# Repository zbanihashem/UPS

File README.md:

# Smart UPS V1

A Raspberry Pi Pico based smart UPS designed for reliable backup power, battery protection, fault monitoring, and system status indication.

The project includes custom PCBs, embedded firmware, sensor monitoring, automatic mains/battery switching, and protection logic.

## V1 Goals

The primary goal of V1 is to build and operate a stable UPS prototype under real load for an extended test period.

V1 is intentionally focused on reliability rather than adding new features. The system is planned to operate for approximately four months so that hardware and firmware issues can be identified before designing V2.

## System Architecture

The system is divided into several functional sections:

- Control Board — Raspberry Pi Pico, RTC, OLED, buzzer and interfaces
- Power Board — power-path control, load switching and power monitoring
- Battery Board — battery temperature and gas monitoring
- LED Board — six system status indicators
- Firmware — fault detection, system policy, power control and display logic

## Firmware Architecture

The firmware is divided into independent modules:

- `Hardware` — low-level GPIO and hardware access
- `Sensors` — sensor acquisition
- `FaultEngine` — fault detection and fault levels
- `SystemPolicy` — system decisions based on detected faults
- `PowerControl` — load, charger and system-power control
- `DisplayManager` — OLED and LED status indication

Main firmware entry point:

`Firmware/UPSPhase1.ino`

## Current V1 Status

The core UPS power-control system is operational.

Verified functions include:

- Automatic startup when mains power is available
- Automatic transition from mains to battery
- Automatic transition back to mains
- Pico self-power hold while operating from battery
- Load disconnect on critical battery condition
- Charger inhibit control
- Complete control-system shutdown on critical battery condition
- Automatic restart when mains power returns
- Mains presence detection
- Battery voltage and current monitoring
- Battery temperature monitoring
- MQ-2 gas monitoring
- OLED status display
- RTC operation
- Buzzer control
- Six front-panel status LEDs

## Status LEDs

The front panel provides six indicators:

- Green — Mains
- Red — Fault
- White — Load
- Blue — Charge Enabled
- Yellow — Battery Operation
- Red — Critical / Danger

The Charge LED represents charger permission from the controller. It does not indicate measured charging current.

## Known V1 Limitations

V1 contains several hardware compromises discovered during integration testing.

These include:

- Passive diode OR power-path architecture
- Relay-based high-side load switching
- Charger module parasitic battery consumption
- Hardware modifications made during integration testing

These issues are being documented for correction in V2.

The current charger isolation issue will be addressed in V1 before extended operation.

## Repository Structure

- `Firmware/` — Raspberry Pi Pico firmware
- `Hardware/` — KiCad schematics, PCB designs and hardware documentation
- `Simulations/` — circuit simulations
- `README.md` — project overview and current status

## Development Strategy

V1 will be operated under real load for approximately four months.

During this period:

- faults and unexpected behavior will be recorded
- hardware modifications will be documented
- firmware changes will be version controlled
- design improvements will be collected for V2

V2 will incorporate the lessons learned from extended V1 operation.

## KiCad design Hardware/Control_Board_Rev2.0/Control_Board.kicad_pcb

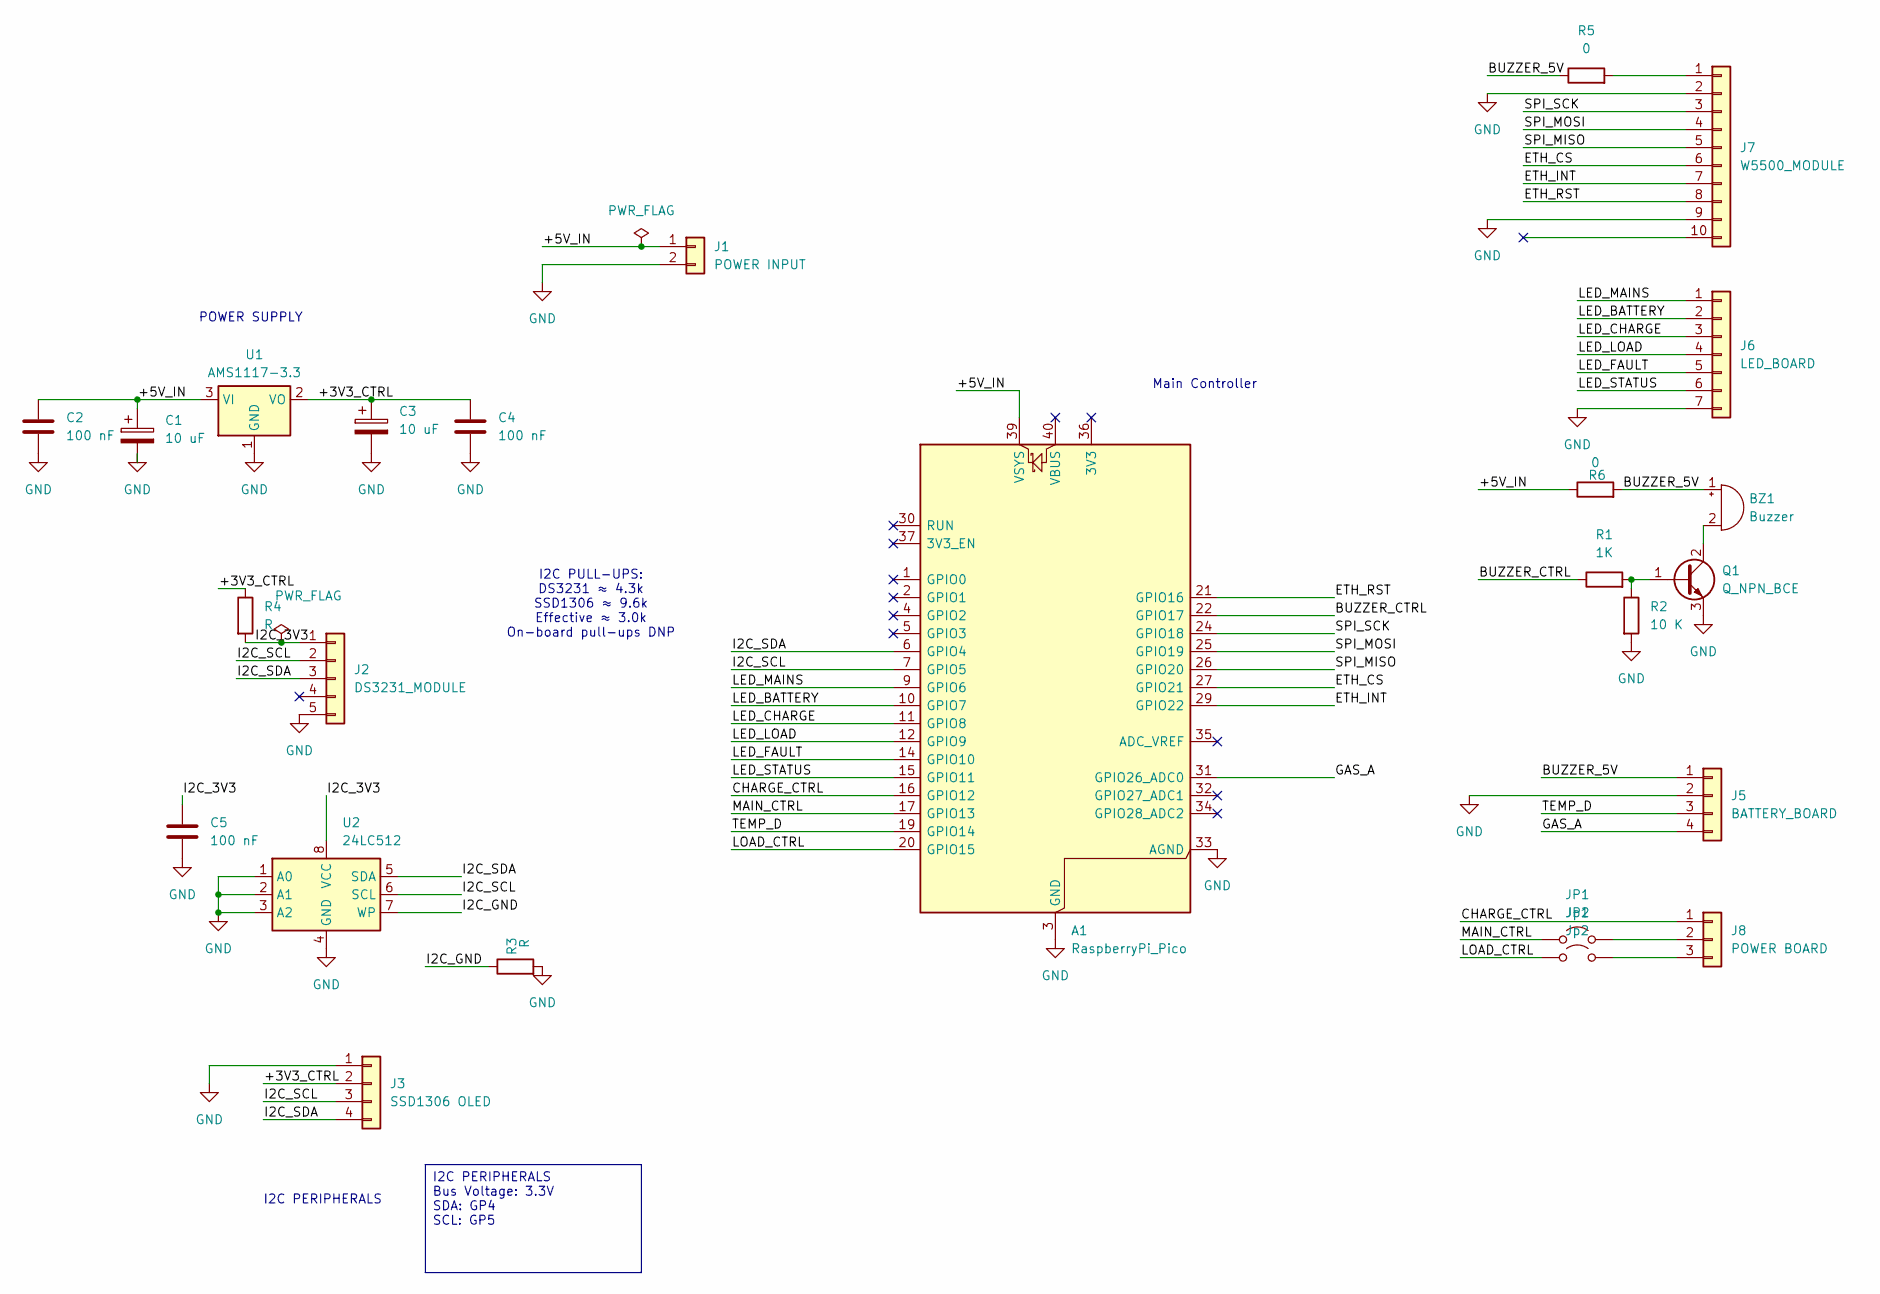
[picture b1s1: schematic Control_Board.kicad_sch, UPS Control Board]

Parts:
A1: RaspberryPi_Pico; RaspberryPi_Pico_Common_Unspecified
BZ1: Buzzer; Buzzer_12x9.5RM7.6
C1, C3: 10 uF; CP_Radial_D5.0mm_P2.50mm
C2, C4, C5: 100 nF; C_Disc_D4.7mm_W2.5mm_P5.00mm
J1: POWER INPUT; PinHeader_1x02_P2.54mm_Vertical
J2: DS3231_MODULE; PinHeader_1x05_P2.54mm_Vertical
J3: SSD1306 OLED; PinHeader_1x04_P2.54mm_Vertical
J5: BATTERY_BOARD; PinHeader_1x04_P2.54mm_Vertical
J6: LED_BOARD; PinHeader_1x07_P2.54mm_Vertical
J7: W5500_MODULE; PinHeader_1x10_P2.54mm_Vertical
J8: POWER BOARD; PinHeader_1x03_P2.54mm_Vertical
JP1: Jp1; Jumper_Harwin_S1621_P10.9mm
JP2: Jp2; Jumper_Harwin_S1621_P10.9mm
Q1: Q_NPN_BCE; TO-92-Large
R1: 1K; R_Axial_DIN0207_L6.3mm_D2.5mm_P10.16mm_Horizontal
R2: 10 K; R_Axial_DIN0207_L6.3mm_D2.5mm_P10.16mm_Horizontal
R3, R4: R; R_Axial_DIN0207_L6.3mm_D2.5mm_P10.16mm_Horizontal
R5, R6: 0; R_Axial_DIN0207_L6.3mm_D2.5mm_P10.16mm_Horizontal
U1: AMS1117-3.3; SOT-223-3_TabPin2
U2: 24LC512; SOIC-8_3.9x4.9mm_P1.27mm

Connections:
/+3V3_CTRL: C3.1, C4.1, J3.2, R4.1, U1.2 (VO)
/+5V_IN: A1.39 (VSYS), C1.1, C2.1, J1.1, R6.1, U1.3 (VI)
/BUZZER_5V: BZ1.1 (+), J5.1, R5.1, R6.2
/BUZZER_CTRL: A1.22 (GPIO17), R1.1
/CHARGE_CTRL: A1.16 (GPIO12), J8.1
/ETH_CS: A1.27 (GPIO21), J7.6
/ETH_INT: A1.29 (GPIO22), J7.7
/ETH_RST: A1.21 (GPIO16), J7.8
/GAS_A: A1.31 (GPIO26_ADC0), J5.4
/I2C_3V3: C5.1, J2.1, R4.2, U2.8 (VCC)
/I2C_GND: R3.1, U2.7 (WP)
/I2C_SCL: A1.7 (GPIO5), J2.2, J3.3, U2.6 (SCL)
/I2C_SDA: A1.6 (GPIO4), J2.3, J3.4, U2.5 (SDA)
/LED_BATTERY: A1.10 (GPIO7), J6.2
/LED_CHARGE: A1.11 (GPIO8), J6.3
/LED_FAULT: A1.14 (GPIO10), J6.5
/LED_LOAD: A1.12 (GPIO9), J6.4
/LED_MAINS: A1.9 (GPIO6), J6.1
/LED_STATUS: A1.15 (GPIO11), J6.6
/LOAD_CTRL: A1.20 (GPIO15), JP2.1 (A)
/MAIN_CTRL: A1.17 (GPIO13), JP1.1 (A)
/SPI_MISO: A1.26 (GPIO20), J7.5
/SPI_MOSI: A1.25 (GPIO19), J7.4
/SPI_SCK: A1.24 (GPIO18), J7.3
/TEMP_D: A1.19 (GPIO14), J5.3
GND: A1.3 (GND), A1.8 (GND), A1.13 (GND), A1.18 (GND), A1.23 (GND), A1.28 (GND), A1.33 (AGND), A1.38 (GND), C1.2, C2.2, C3.2, C4.2, C5.2, J1.2, J2.5, J3.1, J5.2, J6.7, J7.2, J7.9, Q1.3 (E), R2.2, R3.2, U1.1 (GND), U2.1 (A0), U2.2 (A1), U2.3 (A2), U2.4 (GND)
unnamed: BZ1.2 (-), Q1.2 (C)
unnamed: J7.1, R5.2
unnamed: J8.2, JP1.2 (B)
unnamed: J8.3, JP2.2 (B)
unnamed: Q1.1 (B), R1.2, R2.1

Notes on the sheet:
I2C PERIPHERALS
Main Controller
POWER SUPPLY
I2C PULL-UPS: DS3231 ≈ 4.3k SSD1306 ≈ 9.6k Effective ≈ 3.0k On-board pull-ups DNP
I2C PERIPHERALS Bus Voltage: 3.3V SDA: GP4 SCL: GP5

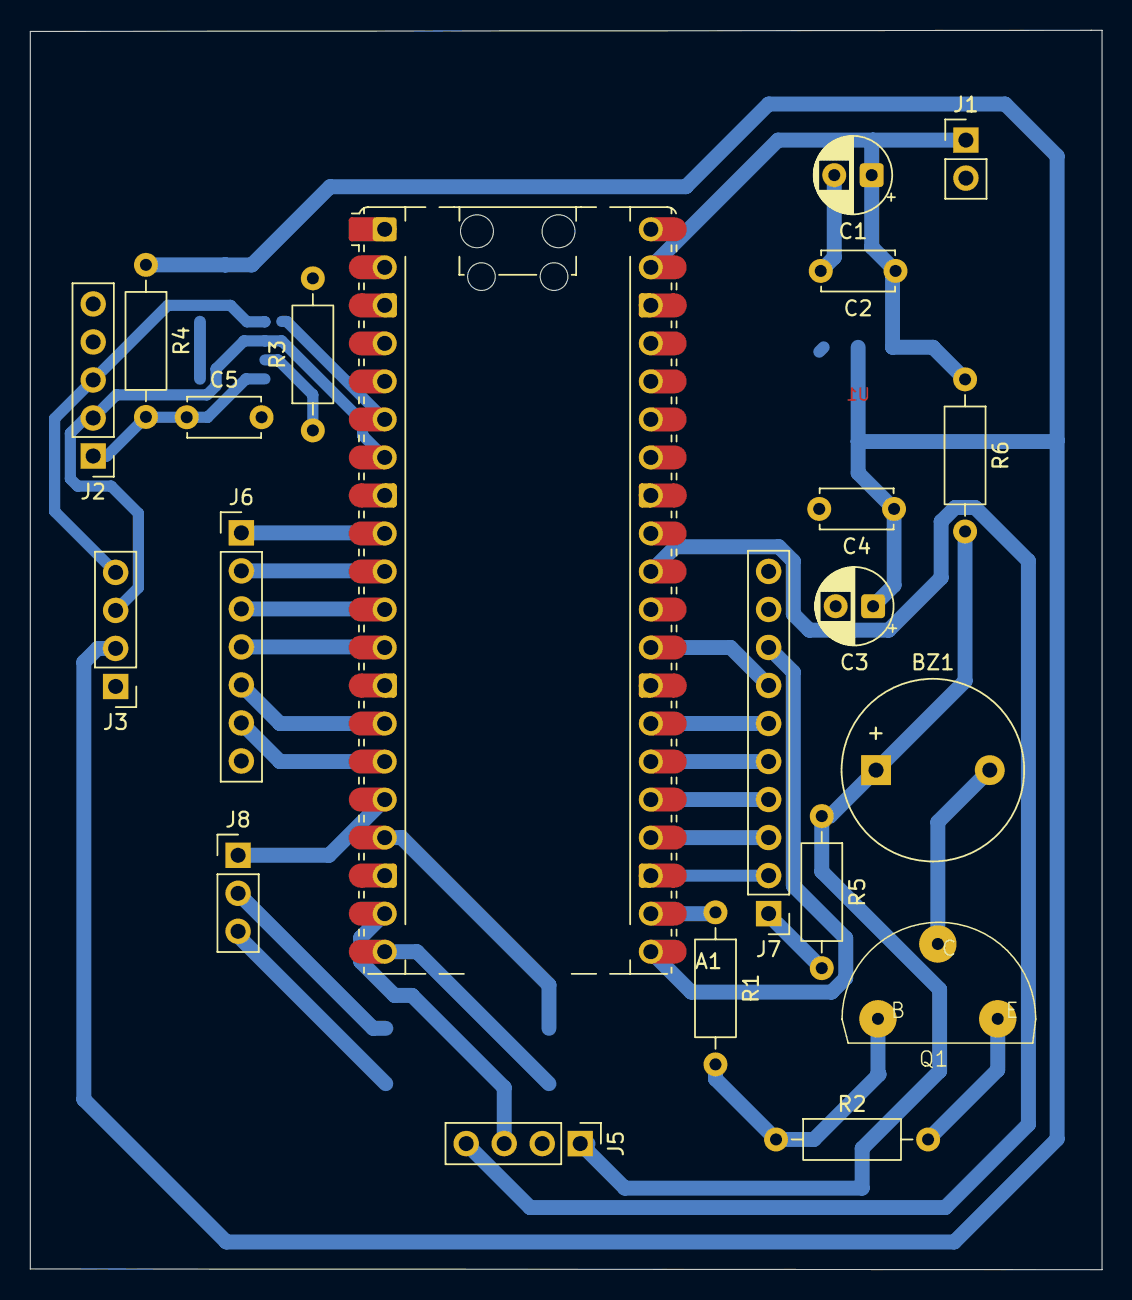
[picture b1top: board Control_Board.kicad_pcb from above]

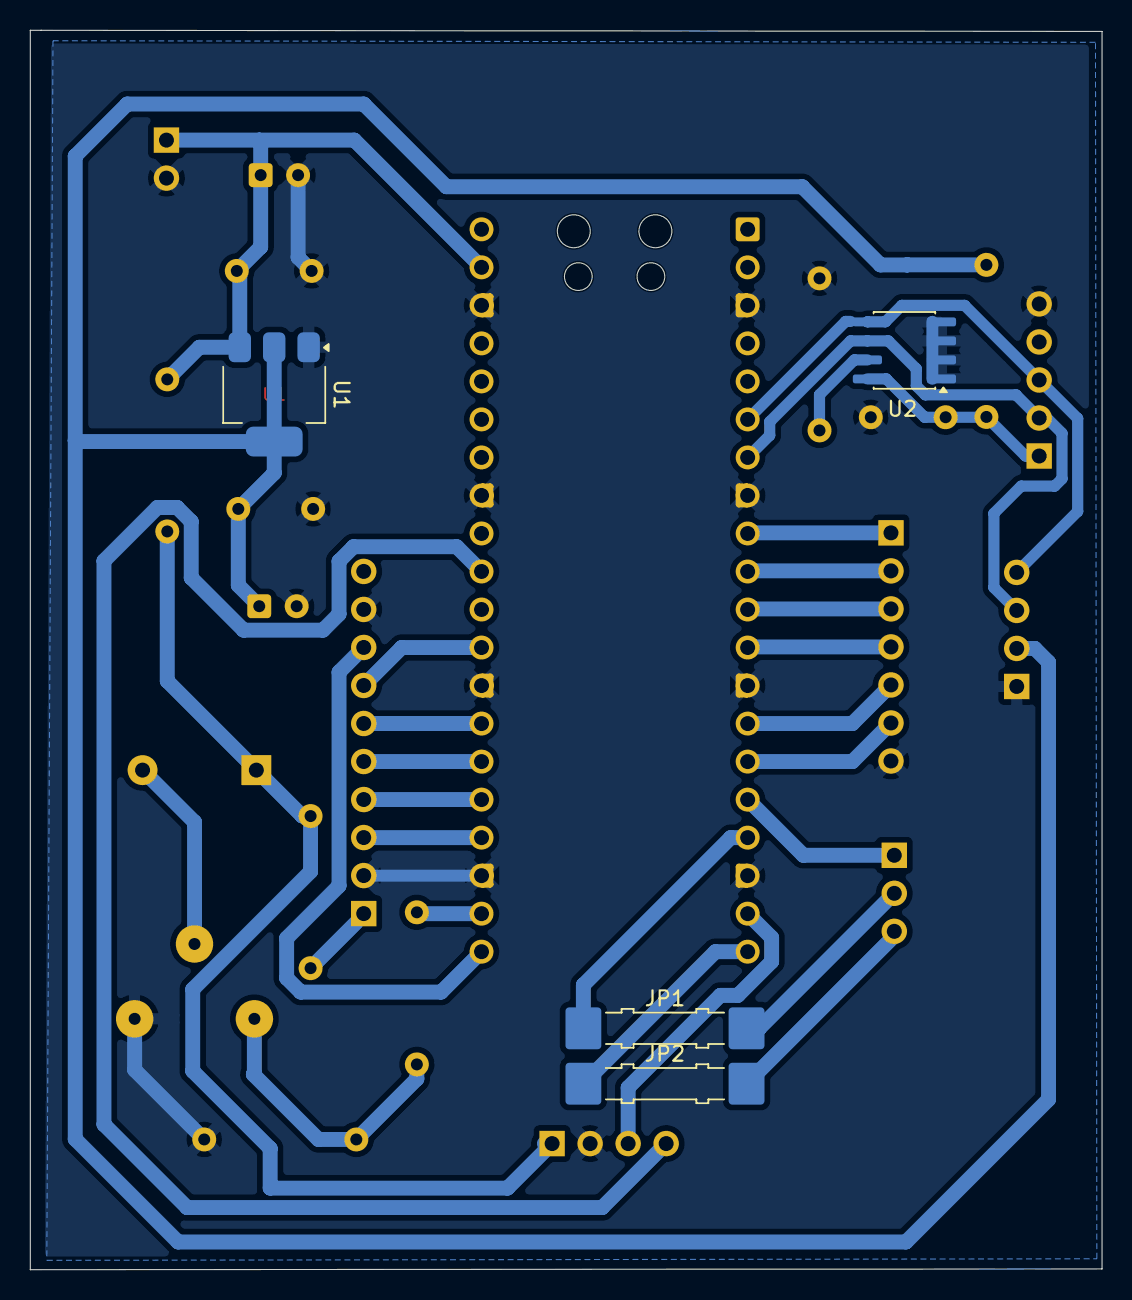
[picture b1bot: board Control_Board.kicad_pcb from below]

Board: 2 copper layers, 71.6 x 82.8 mm, 25 parts (4 on the bottom side), 31 nets.

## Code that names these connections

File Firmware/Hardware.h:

#ifndef HARDWARE_H
#define HARDWARE_H

#include <stdint.h>
#include <Arduino.h>
// ======================= I/O Configuration =============================
#define I2C_ADDRESS   0x40

#define MAINS_SENSE   3

#define I2C_SDA_PIN   4
#define I2C_SCL_PIN   5

#define LED_MAINS     6
#define LED_FAULT     7
#define LED_LOAD      8
#define LED_CHARGE    9
#define LED_BATTERY   10
#define LED_DANGER    11

#define MAIN_PIN      12
#define CHARGE_PIN    13
#define ONE_WIRE_BUS  14
#define LOAD_PIN      15

#define BUZZER_PIN    17

#define MQ2_ADC_PIN   26


struct INAData
{
    float bus_v;
    float sunt_mv;
    float current;
    float power;
};

namespace HW {

    
    void init();

    // --- Voltage / Current (INA, ADC, etc.) ---
    void ReadINA(INAData&); 
    
    // --- Gas sensor ---
    float ReadGas();

    // --- Temperature (OneWire) ---
    float ReadTemperature();

    void SetBuzzer(bool buzzerState);

    // --- Outputs ---
    void SetMainsLED(bool state);
    void SetBatteryLED(bool state);
    void SetChargeLED(bool state);    
    void SetLoadLED(bool state);
    void SetFaultLED(bool state);
    void SetDangerLED(bool state);

    void ControlMain(bool mainState);
    void ControlLoad(bool loadState);
    void ControlCharge(bool chargeState);
    bool IsMainsPresent();
    

}

#endif
